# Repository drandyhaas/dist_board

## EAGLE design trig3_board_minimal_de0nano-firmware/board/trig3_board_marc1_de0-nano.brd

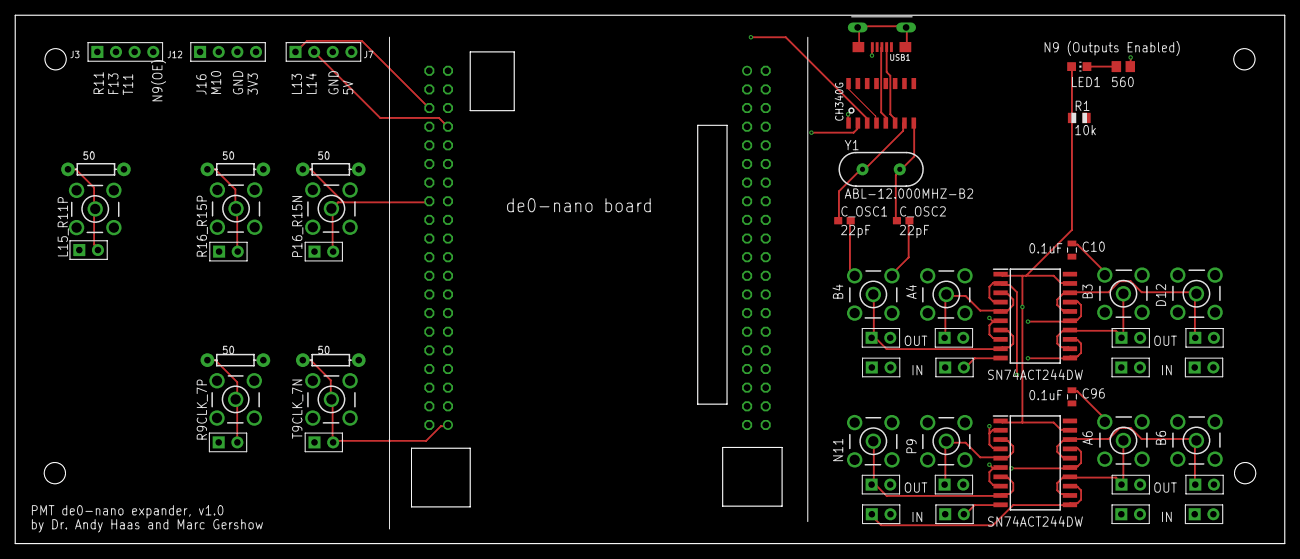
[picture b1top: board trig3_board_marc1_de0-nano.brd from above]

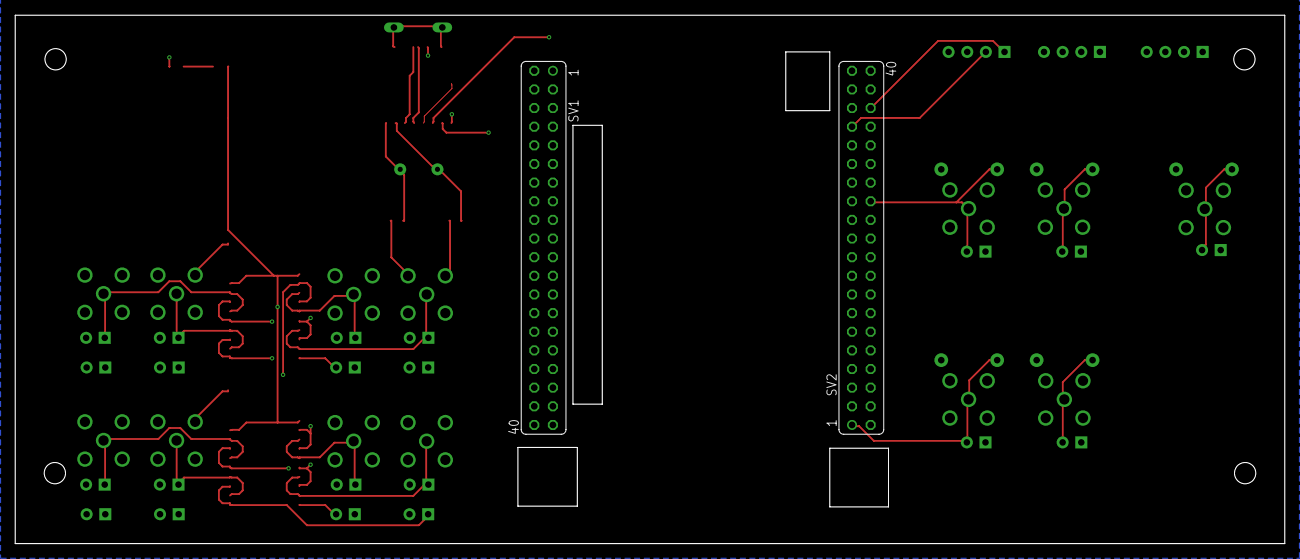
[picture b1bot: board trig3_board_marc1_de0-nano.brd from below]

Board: 4 copper layers, 173.0 x 72.0 mm, 56 parts (2 on the bottom side), 39 nets.

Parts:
A4, A6: BU-SMB-V
B3, B4, B6: BU-SMB-V
C10, C96: 0.1uF; 0805
C_OSC1, C_OSC2: 22pF; C0603
D12: BU-SMB-V
J3, J7, J12: 4p-2.54; H4-2.54
J5, J6, J34, J42, J43: 2p-2.54; H2-2.54
L15_R11P: BU-SMB-V
LED1: red; CHIP-LED0805
N11: BU-SMB-V
OJ41, OJ42, OJ43, OJ44, OJ45, OJ46, OJ47, OJ48, OJ89, OJ90, OJ91, OJ92, OJ93, OJ94, OJ95, OJ96: 2p-2.54; H2-2.54
P9, P16_R15N: BU-SMB-V
R1: 10k; R0805
R5, R6, R31, R41, R43: 50; AXIAL-0.3
R8: 560; R0805
R9CLK_7P, R16_R15P: BU-SMB-V
SV1, SV2: FE20-2
T9CLK_7N: BU-SMB-V
U340G: CH340G; SOIC16
USB1: MF-CON-MICROUSB-RIGHT; 10118193-0001LF
VSLUE5, VSLUE11: SN74ACT244DW; SOIC127P1030X265-20N
Y1: ABL-12.000MHZ-B2; HC49US

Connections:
3V3: J12.4, SV1.29, SV2.29
5V: C10.2, C96.2, J7.4, R1.2, SV1.11, SV2.11, USB1.1, VSLUE5.20, VSLUE11.20
+3V3: U340G.4, U340G.16
DMINUS: U340G.6, USB1.2
DPLUS: U340G.5, USB1.3
GND: A4.2, A4.3, A4.4, A4.5, A6.2, A6.3, A6.4, A6.5, B3.2, B3.3, B3.4, B3.5, B4.2, B4.3, B4.4, B4.5, B6.2, B6.3, B6.4, B6.5, C10.1, C96.1, C_OSC1.2, C_OSC2.2, D12.2, D12.3, D12.4, D12.5, J5.1, J6.1, J7.3, J12.3, J34.1, J42.1, J43.1, L15_R11P.2, L15_R11P.3, L15_R11P.4, L15_R11P.5, N11.2, N11.3, N11.4, N11.5, OJ41.2, OJ42.2, OJ43.2, OJ44.2, OJ45.2, OJ46.2, OJ47.2, OJ48.2, OJ89.2, OJ90.2, OJ91.2, OJ92.2, OJ93.2, OJ94.2, OJ95.2, OJ96.2, P9.2, P9.3, P9.4, P9.5, P16_R15N.2, P16_R15N.3, P16_R15N.4, P16_R15N.5, R5.P$1, R6.P$1, R8.2, R9CLK_7P.2, R9CLK_7P.3, R9CLK_7P.4, R9CLK_7P.5, R16_R15P.2, R16_R15P.3, R16_R15P.4, R16_R15P.5, R31.P$1, R41.P$1, R43.P$1, SV1.12, SV1.30, SV2.12, SV2.30, T9CLK_7N.2, T9CLK_7N.3, T9CLK_7N.4, T9CLK_7N.5, U340G.1, USB1.5, VSLUE5.10, VSLUE11.10
GPIO_1_IN0_T9CLK: J6.2, R6.P$2, SV2.1, T9CLK_7N.1
GPIO_1_IN1_R9CLK: J5.2, R5.P$2, R9CLK_7P.1, SV2.3
GPIO_04_B3: OJ96.1, SV1.7, VSLUE11.6, VSLUE11.8
GPIO_05_B4: OJ94.1, SV1.8, VSLUE11.11, VSLUE11.13
GPIO_06_A4: OJ93.1, SV1.9, VSLUE11.15, VSLUE11.17
GPIO_010_B6: OJ47.1, SV1.15, VSLUE5.2, VSLUE5.4
GPIO_10_F13: J3.2, SV2.2
GPIO_011_A6: OJ48.1, SV1.16, VSLUE5.6, VSLUE5.8
GPIO_17_T11: J3.3, SV2.10
GPIO_19_R11: J3.1, SV2.14
GPIO_032_D12: OJ95.1, SV1.39, VSLUE11.2, VSLUE11.4
GPIO_113_P9: OJ45.1, SV2.18, VSLUE5.15, VSLUE5.17
GPIO_114_N9: J3.4, LED1.A, R1.1, SV2.19, VSLUE5.1, VSLUE5.19, VSLUE11.1, VSLUE11.19
GPIO_115_N11: OJ46.1, SV2.20, VSLUE5.11, VSLUE5.13
GPIO_118_R16: J34.2, R16_R15P.1, R31.P$2, SV2.23
GPIO_119_L15: J43.2, L15_R11P.1, R43.P$2, SV2.24
GPIO_121_P16: J42.2, P16_R15N.1, R41.P$2, SV2.26
GPIO_126_L14: J7.2, SV2.33, U340G.3
GPIO_128_M10: J12.2, SV2.35
GPIO_129_L13: J7.1, SV2.36, U340G.2
GPIO_130_J16: J12.1, SV2.37
unnamed: LED1.C, R8.1
unnamed: C_OSC1.1, U340G.7, Y1.1
unnamed: C_OSC2.1, U340G.8, Y1.2
OUT21: B6.1, OJ44.1, VSLUE5.16, VSLUE5.18
OUT22: A6.1, OJ43.1, VSLUE5.12, VSLUE5.14
OUT23: OJ41.1, P9.1, VSLUE5.3, VSLUE5.5
OUT24: N11.1, OJ42.1, VSLUE5.7, VSLUE5.9
OUT45: D12.1, OJ92.1, VSLUE11.16, VSLUE11.18
OUT46: B3.1, OJ91.1, VSLUE11.12, VSLUE11.14
OUT47: A4.1, OJ89.1, VSLUE11.3, VSLUE11.5
OUT48: B4.1, OJ90.1, VSLUE11.7, VSLUE11.9
SLD: USB1.S1, USB1.S2, USB1.S3, USB1.S4

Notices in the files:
parts and their libraries:
SparkFun-Capacitors: Licensing: Creative Commons ShareAlike 4.0 International - https://creativecommons.org/licenses/by-sa/4.0
